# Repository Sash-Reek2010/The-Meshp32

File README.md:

# The Meshp32
An ESP32 based devboard who's main purpose is to run Meshtastic firmware! It has 22 pins broken out which can be used to attach an external screen and keyboard to transmit messages or even speakers for auditory output. It has a TP4056 so it can become a portable rechargable mestastic node in itself! It aslo features the SX126 as the LoRA board required for Meshtastic! In all, the components cost around 16 dollars in LCSC.

# The Devboard

## The Schematic
This schematic is made in KiCAD!

## The PCB
This PCB is also made in KiCAD!

## PCB View

## Case

## Try it out!

[KiCanvas Link](https://kicanvas.org/?repo=https%3A%2F%2Fgithub.com%2FSash-Reek2010%2FThe-Meshp32%2Ftree%2Fmain%2FSource%2FKiCAD)

## Meshtastic Firmware

https://github.com/meshtastic/meshtastic

## Thanks for reading :D -Sashreek!

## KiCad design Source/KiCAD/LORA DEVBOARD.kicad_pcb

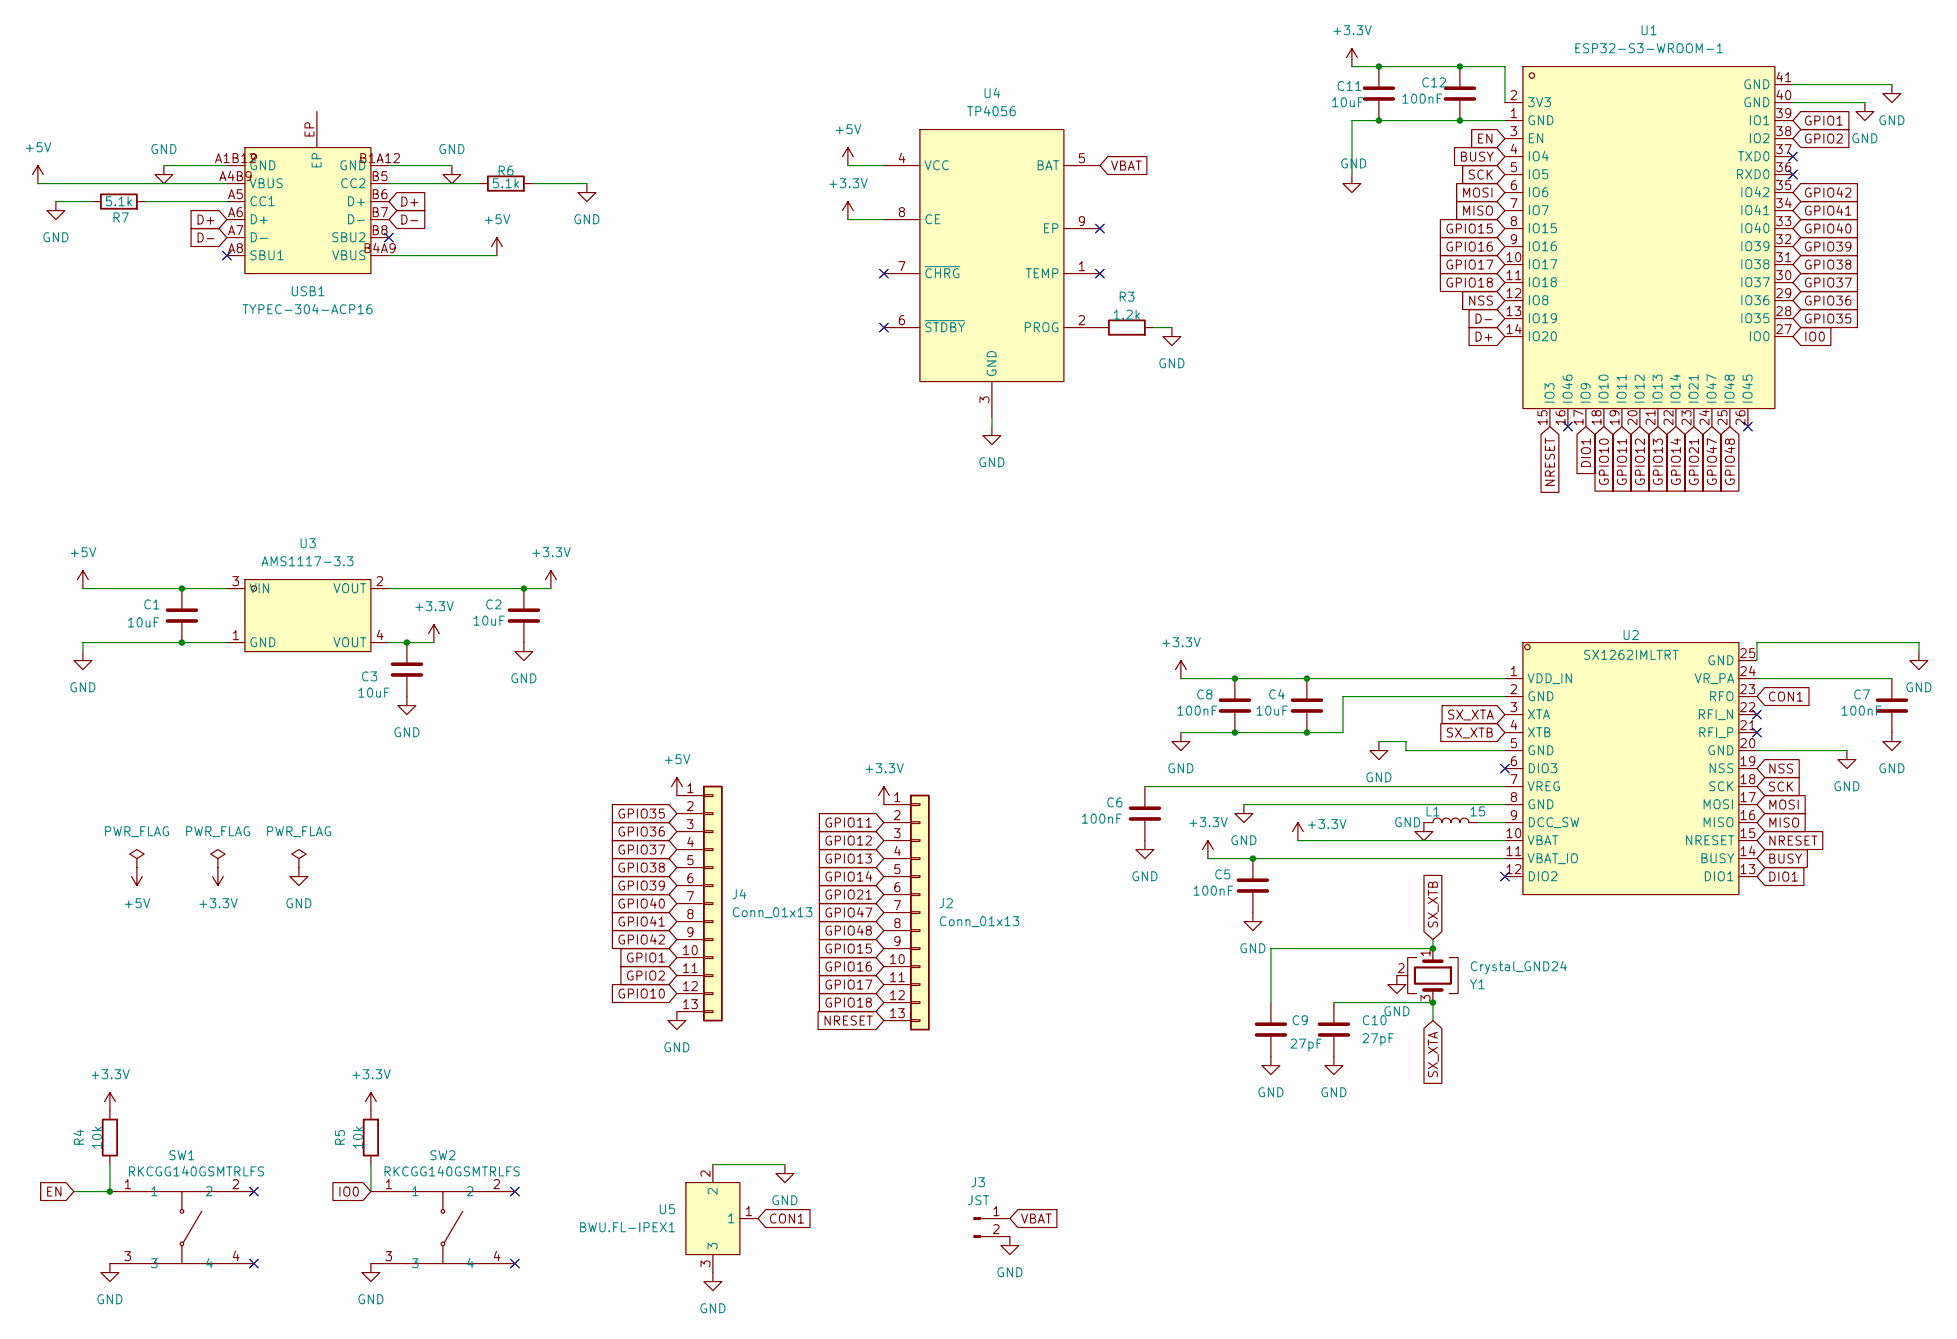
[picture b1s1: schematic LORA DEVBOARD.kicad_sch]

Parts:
C1, C2, C3, C4, C11: 10uF; C_0603_1608Metric
C5, C6, C7, C8, C12: 100nF; C_0603_1608Metric
C9, C10: 27pF; C_0603_1608Metric
J2, J4: Conn_01x13; PinHeader_1x13_P2.54mm_Vertical
J3: JST; JST_EH_B2B-EH-A_1x02_P2.50mm_Vertical
L1: 15; L_0603_1608Metric
R3: 1.2k; R_0603_1608Metric
R4, R5: 10k; R_0603_1608Metric
R6, R7: 5.1k; R_0603_1608Metric
SW1, SW2: RKCGG140GSMTRLFS; SW-SMD_4P-L3.0-W2.6-P1.80-LS3.5; MPN RKCGG140GSMTRLFS; LCSC Part C2927791
U1: ESP32-S3-WROOM-1; WIRELM-SMD_ESP32-S3-WROOM-1; MPN ESP32-S3-WROOM-1-N16R2; LCSC Part C2913205
U2: SX1262IMLTRT; QFN-24_L4.0-W4.0-P0.50-BL-EP2.6; MPN SX1262IMLTRT; LCSC Part C191341
U3: AMS1117-3.3; SOT-223-3_L6.5-W3.4-P2.30-LS7.0-BR; MPN AMS1117-3.3; LCSC Part C6186
U4: TP4056; ESOP-8_L4.9-W3.9-P1.27-LS6.0-BL-EP; MPN TP4056-42-ESOP8; LCSC Part C16581
U5: BWU.FL-IPEX1; IPEX-SMD_BWIPX-1-001E; MPN BWU.FL-IPEX1; LCSC Part C5137195
USB1: TYPEC-304-ACP16; USB-C-SMD_TYPE-C-16P-1; MPN TYPEC-304-ACP16; LCSC Part C2982555
Y1: Crystal_GND24; Crystal_SMD_3225-4Pin_3.2x2.5mm

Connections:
+3.3V: C2.2, C3.2, C4.2, C5.2, C8.2, C11.2, C12.2, J2.1, R4.2, R5.2, U1.2 (3V3), U2.1 (VDD_IN), U2.10 (VBAT), U2.11 (VBAT_IO), U3.2 (VOUT), U3.4 (VOUT), U4.8 (CE)
+5V: C1.2, J4.1, U3.3 (VIN), U4.4 (VCC), USB1.A4B9 (VBUS), USB1.B4A9 (VBUS)
BUSY: U1.4 (IO4), U2.14 (BUSY)
CON1: U2.23 (RFO), U5.1
D+: U1.14 (IO20), USB1.A6 (D+), USB1.B6 (D+)
D-: U1.13 (IO19), USB1.A7 (D-), USB1.B7 (D-)
DIO1: U1.17 (IO9), U2.13 (DIO1)
EN: R4.1, SW1.1, U1.3 (EN)
GND: C1.1, C2.1, C3.1, C4.1, C5.1, C6.1, C7.1, C8.1, C9.2, C10.2, C11.1, C12.1, J3.2, J4.13, L1.1, R3.2, R6.2, R7.1, SW1.3, SW2.3, U1.1 (GND), U1.40 (GND), U1.41 (GND), U2.2 (GND), U2.5 (GND), U2.8 (GND), U2.20 (GND), U2.25 (GND), U3.1 (GND), U4.3 (GND), U5.2, U5.3, USB1.A1B12 (GND), USB1.B1A12 (GND), Y1.2 (G), Y1.4 (G)
GPIO1: J4.10, U1.39 (IO1)
GPIO2: J4.11, U1.38 (IO2)
GPIO10: J4.12, U1.18 (IO10)
GPIO11: J2.2, U1.19 (IO11)
GPIO12: J2.3, U1.20 (IO12)
GPIO13: J2.4, U1.21 (IO13)
GPIO14: J2.5, U1.22 (IO14)
GPIO15: J2.9, U1.8 (IO15)
GPIO16: J2.10, U1.9 (IO16)
GPIO17: J2.11, U1.10 (IO17)
GPIO18: J2.12, U1.11 (IO18)
GPIO21: J2.6, U1.23 (IO21)
GPIO35: J4.2, U1.28 (IO35)
GPIO36: J4.3, U1.29 (IO36)
GPIO37: J4.4, U1.30 (IO37)
GPIO38: J4.5, U1.31 (IO38)
GPIO39: J4.6, U1.32 (IO39)
GPIO40: J4.7, U1.33 (IO40)
GPIO41: J4.8, U1.34 (IO41)
GPIO42: J4.9, U1.35 (IO42)
GPIO47: J2.7, U1.24 (IO47)
GPIO48: J2.8, U1.25 (IO48)
IO0: R5.1, SW2.1, U1.27 (IO0)
MISO: U1.7 (IO7), U2.16 (MISO)
MOSI: U1.6 (IO6), U2.17 (MOSI)
NRESET: J2.13, U1.15 (IO3), U2.15 (NRESET)
NSS: U1.12 (IO8), U2.19 (NSS)
unnamed: L1.2, U2.9 (DCC_SW)
unnamed: C6.2, U2.7 (VREG)
unnamed: C7.2, U2.24 (VR_PA)
unnamed: R3.1, U4.2 (PROG)
unnamed: R7.2, USB1.A5 (CC1)
unnamed: R6.1, USB1.B5 (CC2)
SCK: U1.5 (IO5), U2.18 (SCK)
SX_XTA: C10.1, U2.3 (XTA), Y1.3
SX_XTB: C9.1, U2.4 (XTB), Y1.1
VBAT: J3.1, U4.5 (BAT)

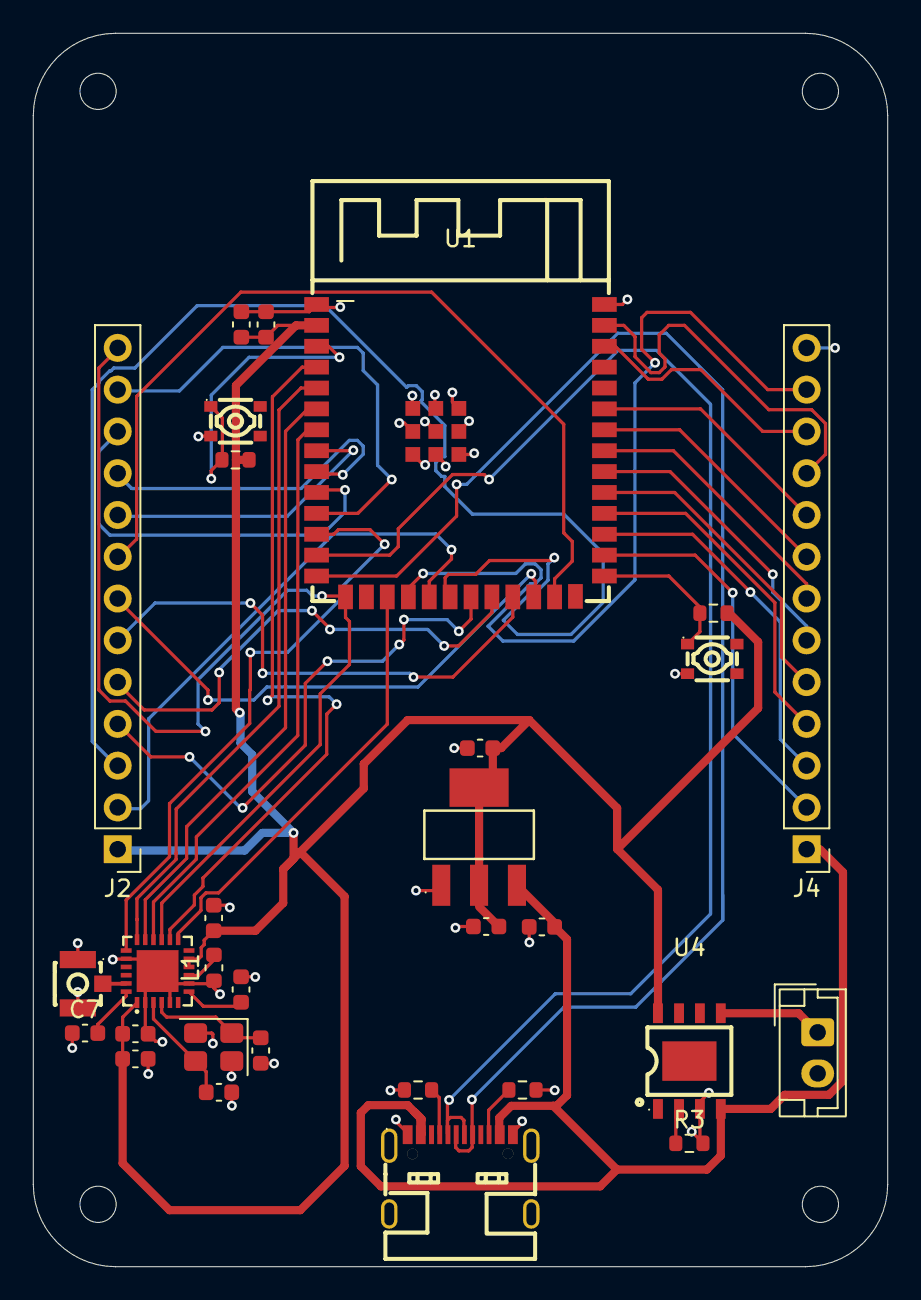
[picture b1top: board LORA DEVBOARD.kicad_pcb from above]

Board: 4 copper layers, 51.9 x 75.0 mm, 30 parts (0 on the bottom side), 46 nets.

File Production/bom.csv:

Designator,Footprint,Quantity,Value,LCSC Part #
"C1, C11, C2, C3, C4",0603,5,10uF,
"C10, C9",0603,2,27pF,
"C12, C5, C6, C7, C8",0603,5,100nF,
"J2, J4",PinHeader_1x13_P2.54mm_Vertical,2,Conn_01x13,
J3,JST_EH_B2B-EH-A_1x02_P2.50mm_Vertical,1,JST,
L1,0603,1,15,
R3,0603,1,1.2k,
"R4, R5",0603,2,10k,
"R6, R7",0603,2,5.1k,
"SW1, SW2",SW-SMD_4P-L3.0-W2.6-P1.80-LS3.5,2,RKCGG140GSMTRLFS,C2927791
U1,WIRELM-SMD_ESP32-S3-WROOM-1,1,ESP32-S3-WROOM-1,C2913205
U2,QFN-24_L4.0-W4.0-P0.50-BL-EP2.6,1,SX1262IMLTRT,C191341
U3,SOT-223-3_L6.5-W3.4-P2.30-LS7.0-BR,1,AMS1117-3.3,C6186
U4,ESOP-8_L4.9-W3.9-P1.27-LS6.0-BL-EP,1,TP4056,C16581
U5,IPEX-SMD_BWIPX-1-001E,1,BWU.FL-IPEX1,C5137195
USB1,USB-C-SMD_TYPE-C-16P-1,1,TYPEC-304-ACP16,C2982555
Y1,Crystal_SMD_3225-4Pin_3.2x2.5mm,1,Crystal_GND24,

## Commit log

2026-05-15 Add Files
2026-05-16 Add Case
2026-05-21 Update PCB
2026-05-21 Rearrange Files
2026-05-21 Update Case
2026-05-28 Replace Files
